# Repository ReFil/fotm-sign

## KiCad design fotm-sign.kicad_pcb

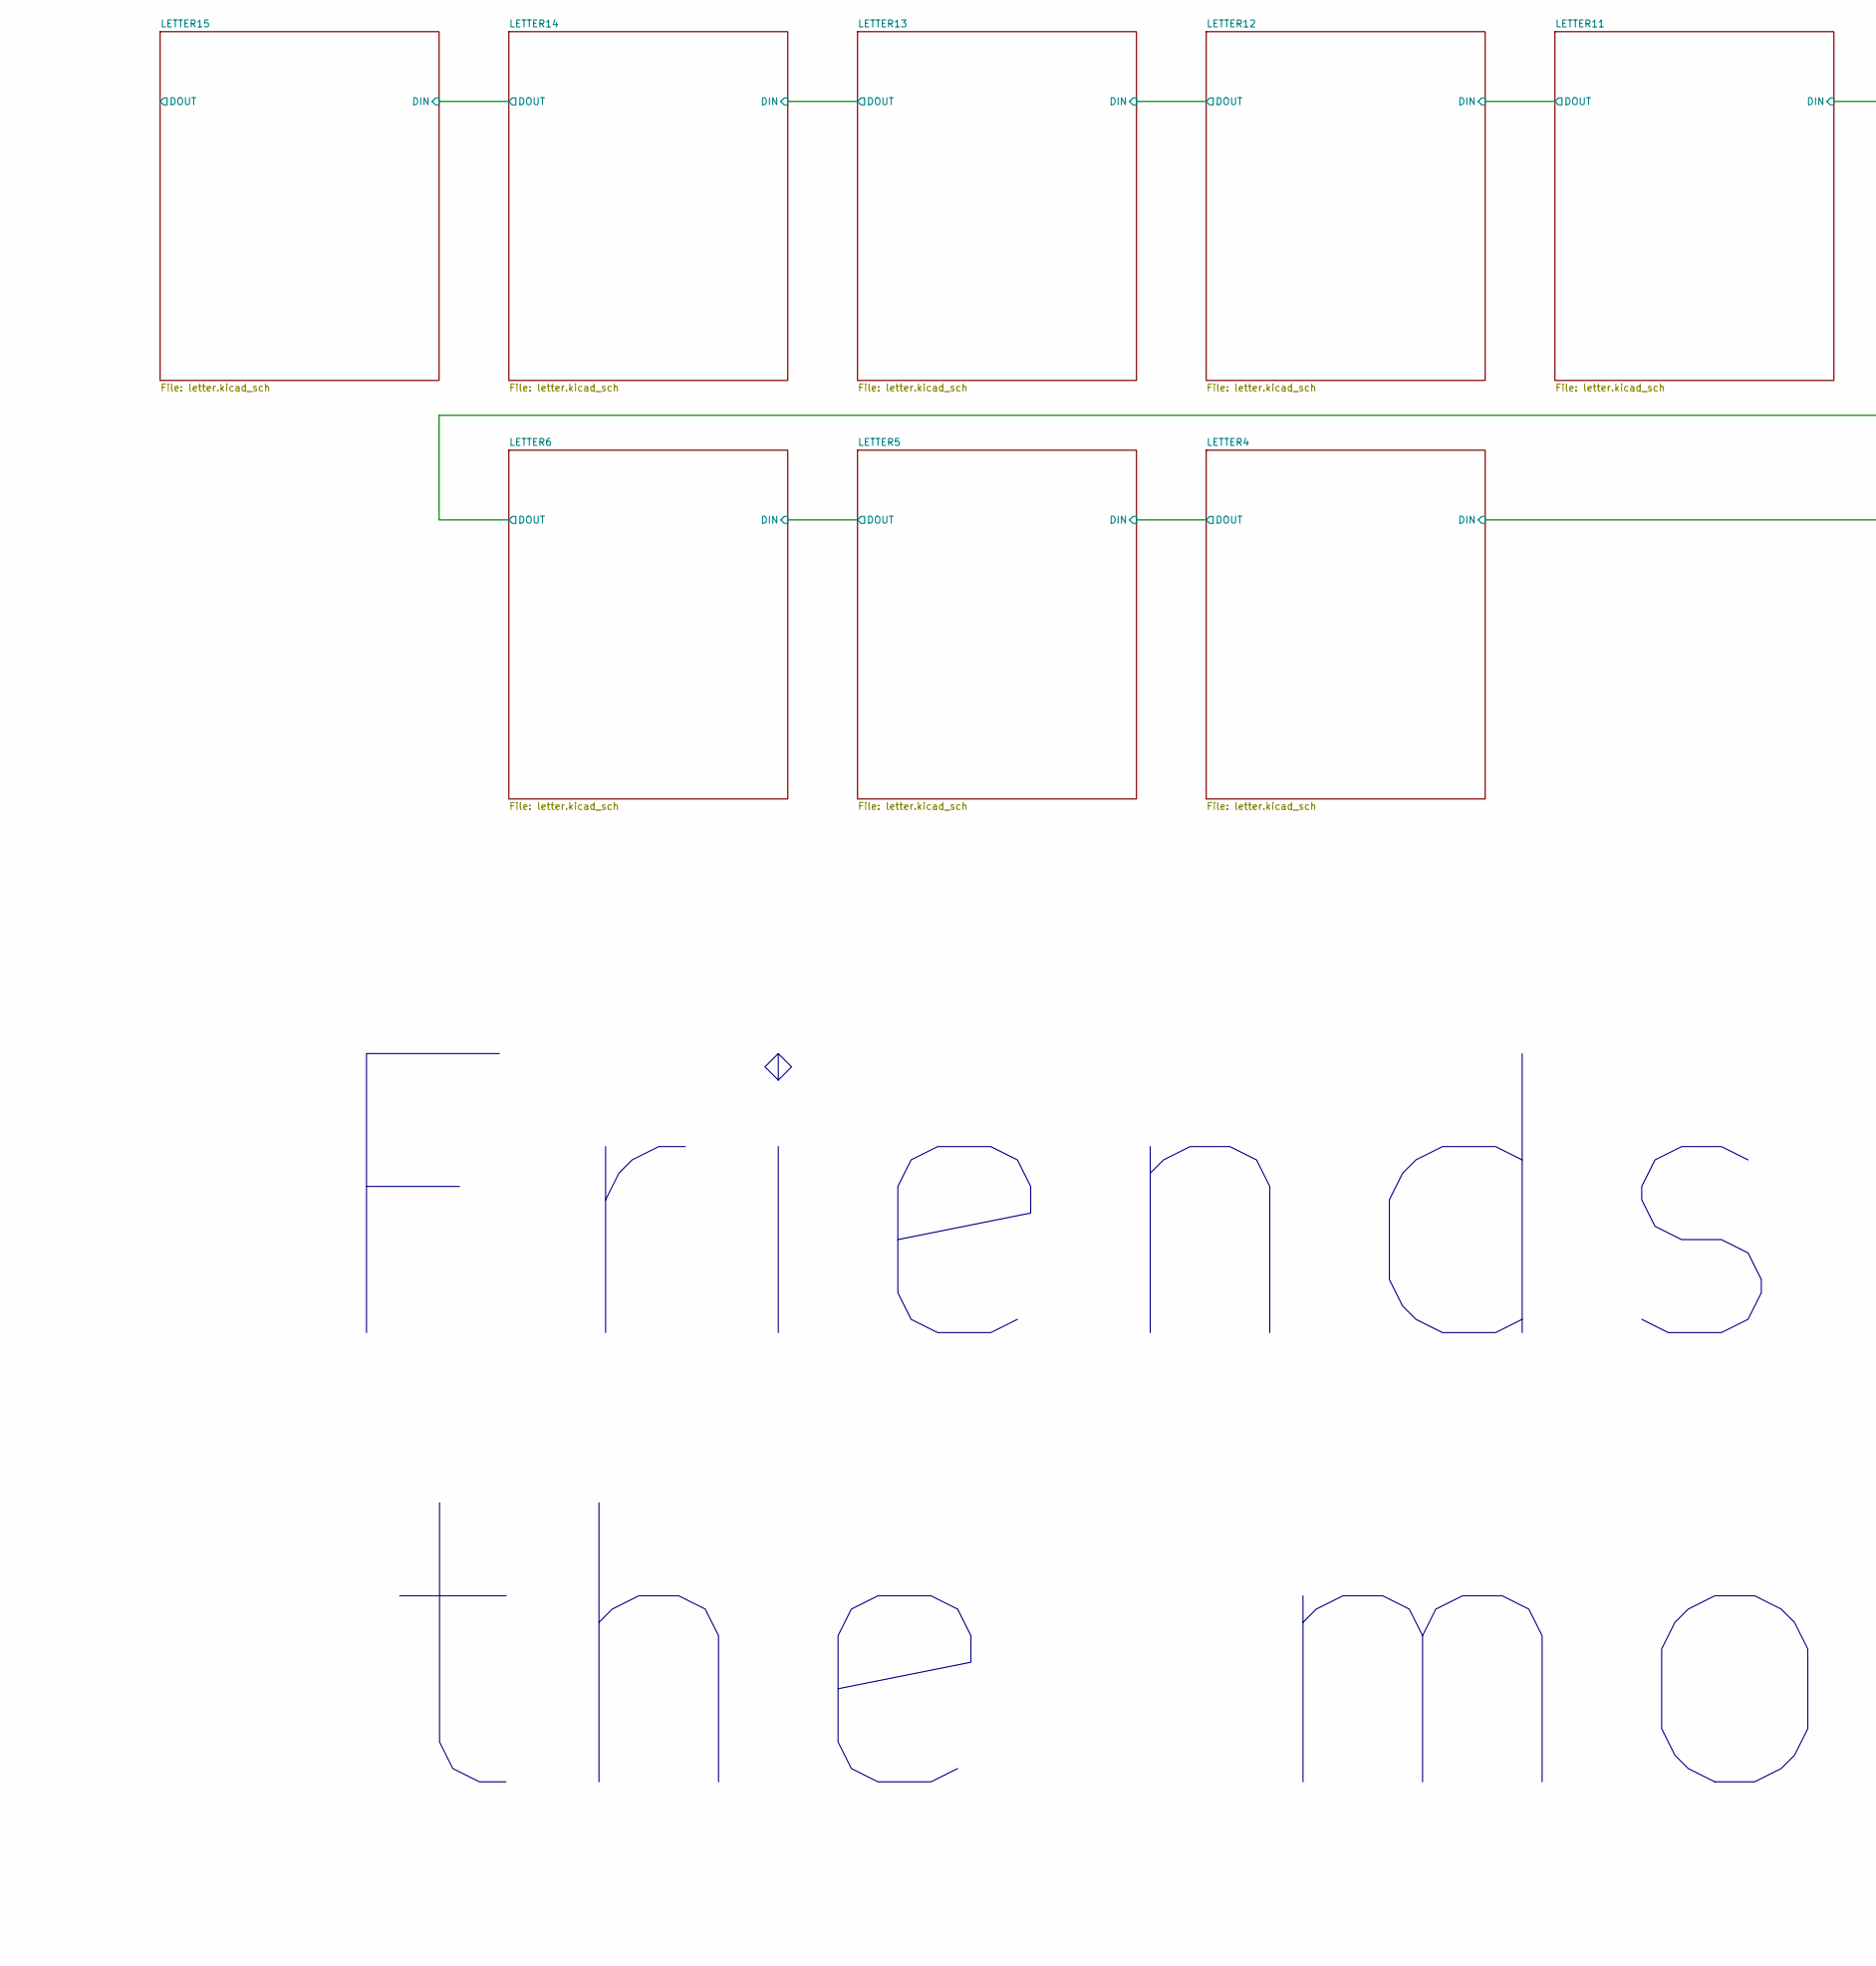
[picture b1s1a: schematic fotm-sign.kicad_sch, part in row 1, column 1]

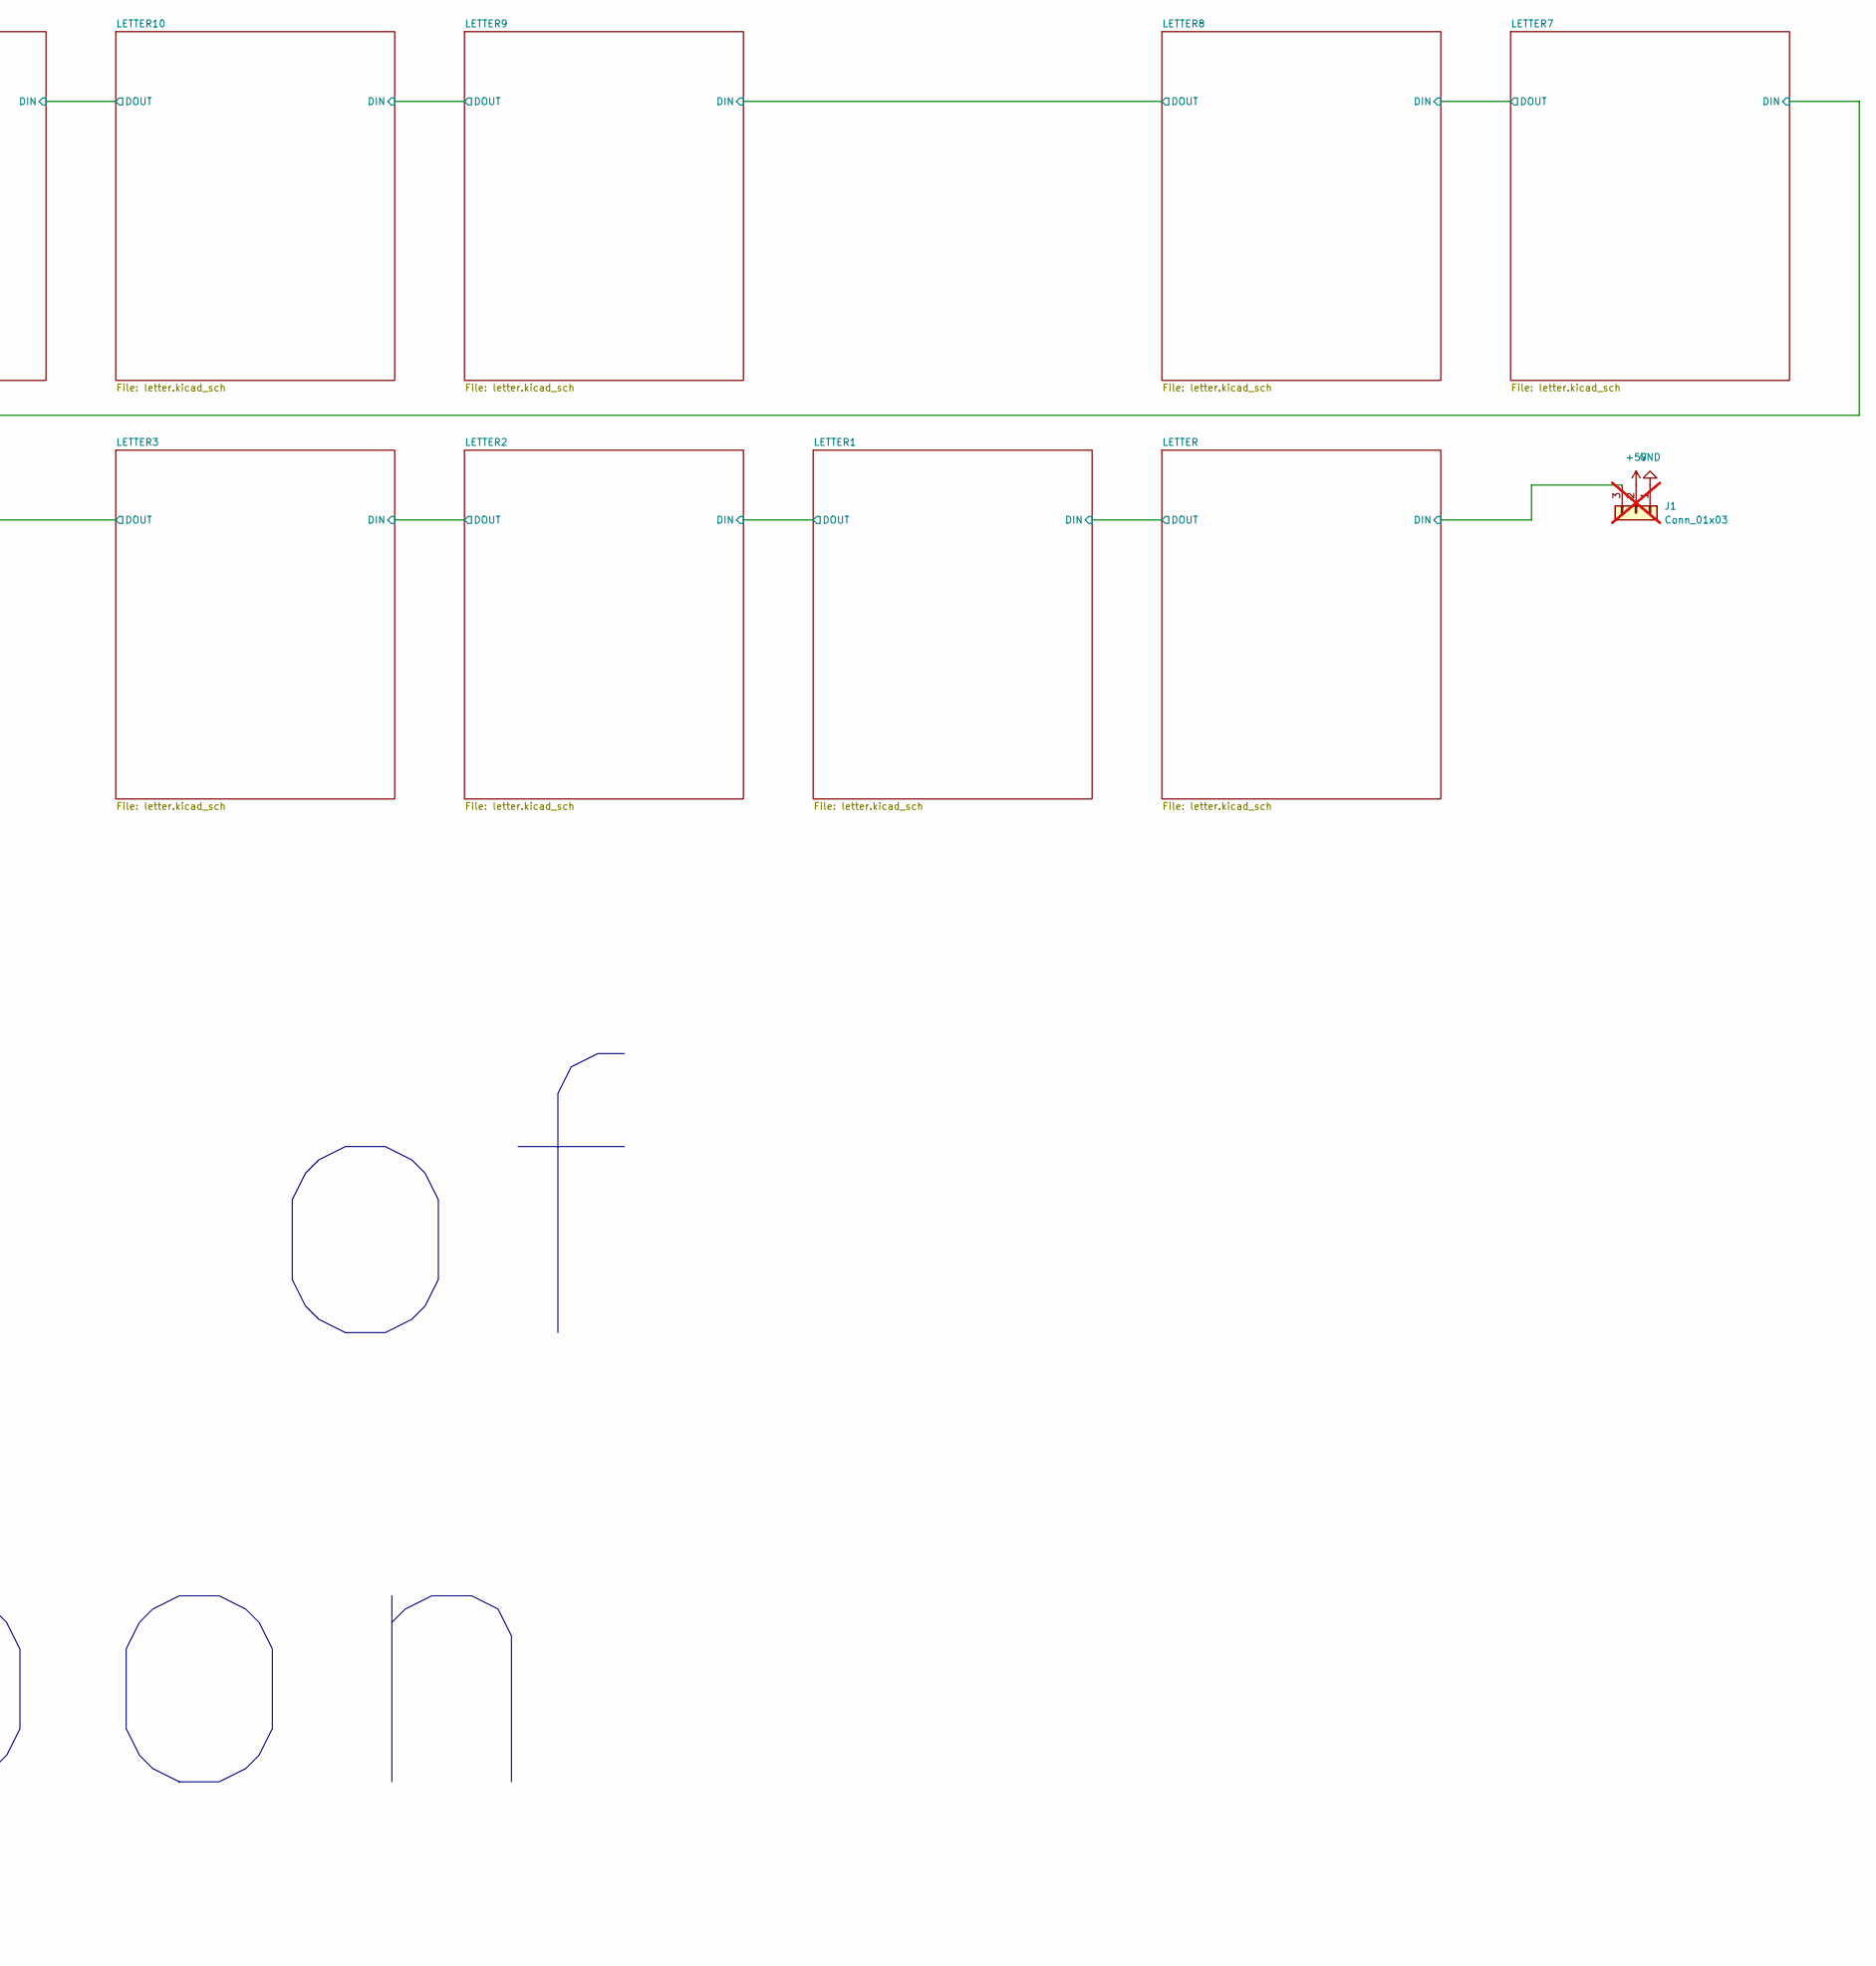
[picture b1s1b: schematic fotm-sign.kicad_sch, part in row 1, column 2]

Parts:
J1: Conn_01x03; PinHeader_1x03_P2.54mm_Vertical; not fitted

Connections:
+5V: J1.2; also elsewhere on the board
/LETTER/DIN: J1.3; also elsewhere on the board
GND: J1.1; also elsewhere on the board

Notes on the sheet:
Friends of the moon

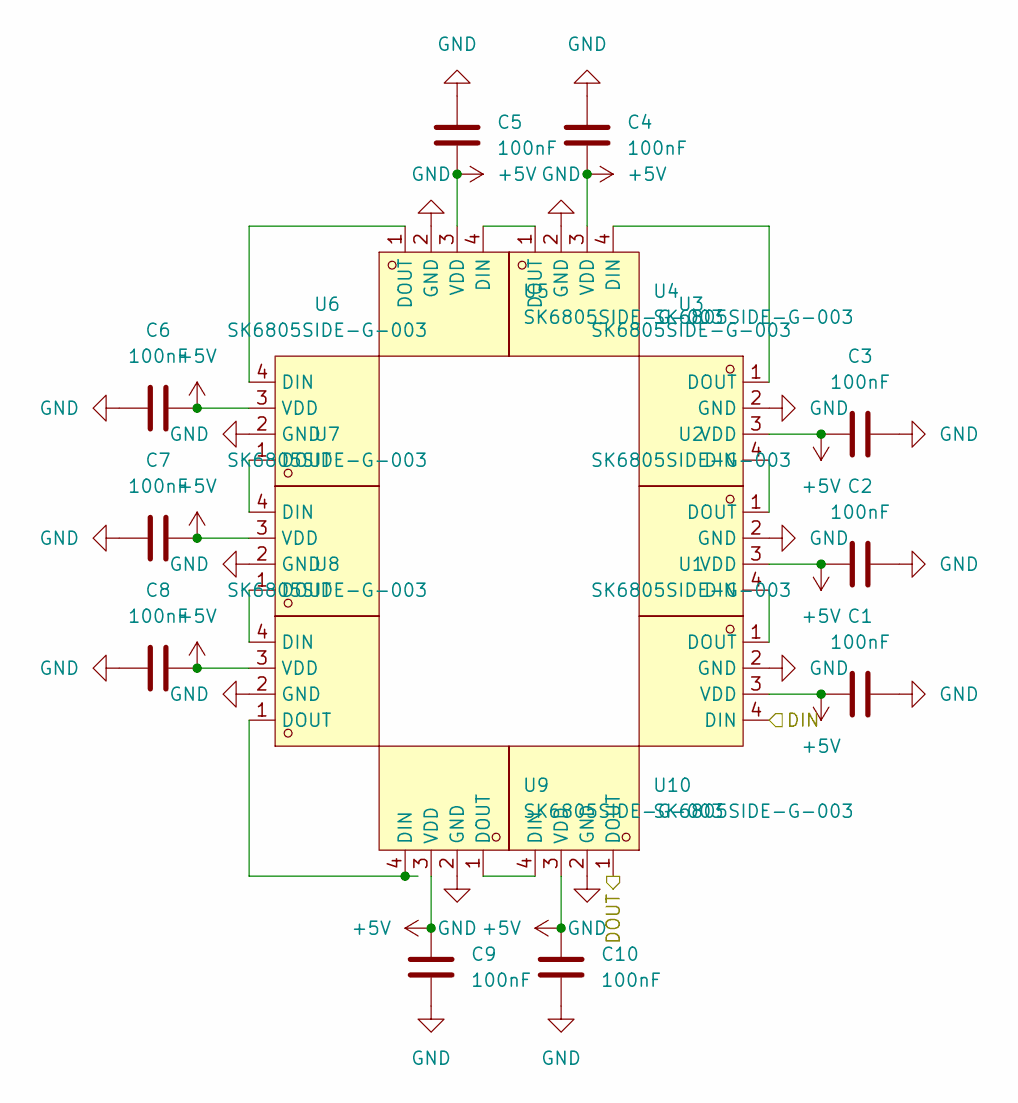
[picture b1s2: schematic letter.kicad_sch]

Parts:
C1, C2, C3, C4, C5, C6, C7, C8, C9, C10: 100nF; C_0402_1005Metric; LCSC Part A
U1, U2, U3, U4, U5, U6, U7, U8, U9, U10: SK6805SIDE-G-003; LED-SMD_4P-L3.5-W1.6_SK6805SIDE-G-001; MPN SK6805SIDE-G-003; LCSC Part C31452139

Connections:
+5V: C1.1, C2.1, C3.1, C4.1, C5.1, C6.1, C7.1, C8.1, C9.1, C10.1, U1.3 (VDD), U2.3 (VDD), U3.3 (VDD), U4.3 (VDD), U5.3 (VDD), U6.3 (VDD), U7.3 (VDD), U8.3 (VDD), U9.3 (VDD), U10.3 (VDD); also elsewhere on the board
/LETTER/DIN: U1.4 (DIN); also elsewhere on the board
/LETTER/DOUT: U10.1 (DOUT); also elsewhere on the board
GND: C1.2, C2.2, C3.2, C4.2, C5.2, C6.2, C7.2, C8.2, C9.2, C10.2, U1.2 (GND), U2.2 (GND), U3.2 (GND), U4.2 (GND), U5.2 (GND), U6.2 (GND), U7.2 (GND), U8.2 (GND), U9.2 (GND), U10.2 (GND); also elsewhere on the board
unnamed: U1.1 (DOUT), U2.4 (DIN)
unnamed: U2.1 (DOUT), U3.4 (DIN)
unnamed: U3.1 (DOUT), U4.4 (DIN)
unnamed: U4.1 (DOUT), U5.4 (DIN)
unnamed: U5.1 (DOUT), U6.4 (DIN)
unnamed: U6.1 (DOUT), U7.4 (DIN)
unnamed: U7.1 (DOUT), U8.4 (DIN)
unnamed: U8.1 (DOUT), U9.4 (DIN)
unnamed: U9.1 (DOUT), U10.4 (DIN)

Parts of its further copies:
C11, C12, C13, C14, C15, C16, C17, C18, C19, C20, C21, C22, C23, C24, C25, C26, C27, C28, C29, C30, C31, C32, C33, C34, C35, C36, C37, C38, C39, C40, C41, C42, C43, C44, C45, C46, C47, C48, C49, C50, C51, C52, C53, C54, C55, C56, C57, C58, C59, C60, C61, C62, C63, C64, C65, C66, C67, C68, C69, C70, C71, C72, C73, C74, C75, C76, C77, C78, C79, C80, C81, C82, C83, C84, C85, C86, C87, C88, C89, C90, C91, C92, C93, C94, C95, C96, C97, C98, C99, C100, C101, C102, C103, C104, C105, C106, C107, C108, C109, C110, C111, C112, C113, C114, C115, C116, C117, C118, C119, C120, C121, C122, C123, C124, C125, C126, C127, C128, C129, C130, C131, C132, C133, C134, C135, C136, C137, C138, C139, C140, C141, C142, C143, C144, C145, C146, C147, C148, C149, C150, C151, C152, C153, C154, C155, C156, C157, C158, C159, C160: 100nF; C_0402_1005Metric; LCSC Part A
U11, U12, U13, U14, U15, U16, U17, U18, U19, U20, U21, U22, U23, U24, U25, U26, U27, U28, U29, U30, U31, U32, U33, U34, U35, U36, U37, U38, U39, U40, U41, U42, U43, U44, U45, U46, U47, U48, U49, U50, U51, U52, U53, U54, U55, U56, U57, U58, U59, U60, U61, U62, U63, U64, U65, U66, U67, U68, U69, U70, U71, U72, U73, U74, U75, U76, U77, U78, U79, U80, U81, U82, U83, U84, U85, U86, U87, U88, U89, U90, U91, U92, U93, U94, U95, U96, U97, U98, U99, U100, U101, U102, U103, U104, U105, U106, U107, U108, U109, U110, U111, U112, U113, U114, U115, U116, U117, U118, U119, U120, U121, U122, U123, U124, U125, U126, U127, U128, U129, U130, U131, U132, U133, U134, U135, U136, U137, U138, U139, U140, U141, U142, U143, U144, U145, U146, U147, U148, U149, U150, U151, U152, U153, U154, U155, U156, U157, U158, U159, U160: SK6805SIDE-G-003; LED-SMD_4P-L3.5-W1.6_SK6805SIDE-G-001; MPN SK6805SIDE-G-003; LCSC Part C31452139

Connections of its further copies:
+5V: C11.1, C12.1, C13.1, C14.1, C15.1, C16.1, C17.1, C18.1, C19.1, C20.1, C21.1, C22.1, C23.1, C24.1, C25.1, C26.1, C27.1, C28.1, C29.1, C30.1, C31.1, C32.1, C33.1, C34.1, C35.1, C36.1, C37.1, C38.1, C39.1, C40.1, C41.1, C42.1, C43.1, C44.1, C45.1, C46.1, C47.1, C48.1, C49.1, C50.1, C51.1, C52.1, C53.1, C54.1, C55.1, C56.1, C57.1, C58.1, C59.1, C60.1, C61.1, C62.1, C63.1, C64.1, C65.1, C66.1, C67.1, C68.1, C69.1, C70.1, C71.1, C72.1, C73.1, C74.1, C75.1, C76.1, C77.1, C78.1, C79.1, C80.1, C81.1, C82.1, C83.1, C84.1, C85.1, C86.1, C87.1, C88.1, C89.1, C90.1, C91.1, C92.1, C93.1, C94.1, C95.1, C96.1, C97.1, C98.1, C99.1, C100.1, C101.1, C102.1, C103.1, C104.1, C105.1, C106.1, C107.1, C108.1, C109.1, C110.1, C111.1, C112.1, C113.1, C114.1, C115.1, C116.1, C117.1, C118.1, C119.1, C120.1, C121.1, C122.1, C123.1, C124.1, C125.1, C126.1, C127.1, C128.1, C129.1, C130.1, C131.1, C132.1, C133.1, C134.1, C135.1, C136.1, C137.1, C138.1, C139.1, C140.1, C141.1, C142.1, C143.1, C144.1, C145.1, C146.1, C147.1, C148.1, C149.1, C150.1, C151.1, C152.1, C153.1, C154.1, C155.1, C156.1, C157.1, C158.1, C159.1, C160.1, U11.3 (VDD), U12.3 (VDD), U13.3 (VDD), U14.3 (VDD), U15.3 (VDD), U16.3 (VDD), U17.3 (VDD), U18.3 (VDD), U19.3 (VDD), U20.3 (VDD), U21.3 (VDD), U22.3 (VDD), U23.3 (VDD), U24.3 (VDD), U25.3 (VDD), U26.3 (VDD), U27.3 (VDD), U28.3 (VDD), U29.3 (VDD), U30.3 (VDD), U31.3 (VDD), U32.3 (VDD), U33.3 (VDD), U34.3 (VDD), U35.3 (VDD), U36.3 (VDD), U37.3 (VDD), U38.3 (VDD), U39.3 (VDD), U40.3 (VDD), U41.3 (VDD), U42.3 (VDD), U43.3 (VDD), U44.3 (VDD), U45.3 (VDD), U46.3 (VDD), U47.3 (VDD), U48.3 (VDD), U49.3 (VDD), U50.3 (VDD), U51.3 (VDD), U52.3 (VDD), U53.3 (VDD), U54.3 (VDD), U55.3 (VDD), U56.3 (VDD), U57.3 (VDD), U58.3 (VDD), U59.3 (VDD), U60.3 (VDD), U61.3 (VDD), U62.3 (VDD), U63.3 (VDD), U64.3 (VDD), U65.3 (VDD), U66.3 (VDD), U67.3 (VDD), U68.3 (VDD), U69.3 (VDD), U70.3 (VDD), U71.3 (VDD), U72.3 (VDD), U73.3 (VDD), U74.3 (VDD), U75.3 (VDD), U76.3 (VDD), U77.3 (VDD), U78.3 (VDD), U79.3 (VDD), U80.3 (VDD), U81.3 (VDD), U82.3 (VDD), U83.3 (VDD), U84.3 (VDD), U85.3 (VDD), U86.3 (VDD), U87.3 (VDD), U88.3 (VDD), U89.3 (VDD), U90.3 (VDD), U91.3 (VDD), U92.3 (VDD), U93.3 (VDD), U94.3 (VDD), U95.3 (VDD), U96.3 (VDD), U97.3 (VDD), U98.3 (VDD), U99.3 (VDD), U100.3 (VDD), U101.3 (VDD), U102.3 (VDD), U103.3 (VDD), U104.3 (VDD), U105.3 (VDD), U106.3 (VDD), U107.3 (VDD), U108.3 (VDD), U109.3 (VDD), U110.3 (VDD), U111.3 (VDD), U112.3 (VDD), U113.3 (VDD), U114.3 (VDD), U115.3 (VDD), U116.3 (VDD), U117.3 (VDD), U118.3 (VDD), U119.3 (VDD), U120.3 (VDD), U121.3 (VDD), U122.3 (VDD), U123.3 (VDD), U124.3 (VDD), U125.3 (VDD), U126.3 (VDD), U127.3 (VDD), U128.3 (VDD), U129.3 (VDD), U130.3 (VDD), U131.3 (VDD), U132.3 (VDD), U133.3 (VDD), U134.3 (VDD), U135.3 (VDD), U136.3 (VDD), U137.3 (VDD), U138.3 (VDD), U139.3 (VDD), U140.3 (VDD), U141.3 (VDD), U142.3 (VDD), U143.3 (VDD), U144.3 (VDD), U145.3 (VDD), U146.3 (VDD), U147.3 (VDD), U148.3 (VDD), U149.3 (VDD), U150.3 (VDD), U151.3 (VDD), U152.3 (VDD), U153.3 (VDD), U154.3 (VDD), U155.3 (VDD), U156.3 (VDD), U157.3 (VDD), U158.3 (VDD), U159.3 (VDD), U160.3 (VDD); also elsewhere on the board
/LETTER1/DOUT: U17.1 (DOUT), U30.4 (DIN)
/LETTER2/DOUT: U27.1 (DOUT), U40.4 (DIN)
/LETTER3/DOUT: U37.1 (DOUT), U50.4 (DIN)
/LETTER4/DOUT: U47.1 (DOUT), U60.4 (DIN)
/LETTER5/DOUT: U57.1 (DOUT), U70.4 (DIN)
/LETTER6/DOUT: U67.1 (DOUT), U80.4 (DIN)
/LETTER7/DOUT: U77.1 (DOUT), U90.4 (DIN)
/LETTER8/DOUT: U87.1 (DOUT), U100.4 (DIN)
/LETTER10/DIN: U97.1 (DOUT), U110.4 (DIN)
/LETTER10/DOUT: U107.1 (DOUT), U120.4 (DIN)
/LETTER11/DOUT: U117.1 (DOUT), U130.4 (DIN)
/LETTER12/DOUT: U127.1 (DOUT), U140.4 (DIN)
/LETTER13/DOUT: U137.1 (DOUT), U150.4 (DIN)
/LETTER14/DOUT: U147.1 (DOUT), U160.4 (DIN)
/LETTER15/DOUT: U157.1 (DOUT)
/LETTER/DOUT: U20.4 (DIN); also elsewhere on the board
GND: C11.2, C12.2, C13.2, C14.2, C15.2, C16.2, C17.2, C18.2, C19.2, C20.2, C21.2, C22.2, C23.2, C24.2, C25.2, C26.2, C27.2, C28.2, C29.2, C30.2, C31.2, C32.2, C33.2, C34.2, C35.2, C36.2, C37.2, C38.2, C39.2, C40.2, C41.2, C42.2, C43.2, C44.2, C45.2, C46.2, C47.2, C48.2, C49.2, C50.2, C51.2, C52.2, C53.2, C54.2, C55.2, C56.2, C57.2, C58.2, C59.2, C60.2, C61.2, C62.2, C63.2, C64.2, C65.2, C66.2, C67.2, C68.2, C69.2, C70.2, C71.2, C72.2, C73.2, C74.2, C75.2, C76.2, C77.2, C78.2, C79.2, C80.2, C81.2, C82.2, C83.2, C84.2, C85.2, C86.2, C87.2, C88.2, C89.2, C90.2, C91.2, C92.2, C93.2, C94.2, C95.2, C96.2, C97.2, C98.2, C99.2, C100.2, C101.2, C102.2, C103.2, C104.2, C105.2, C106.2, C107.2, C108.2, C109.2, C110.2, C111.2, C112.2, C113.2, C114.2, C115.2, C116.2, C117.2, C118.2, C119.2, C120.2, C121.2, C122.2, C123.2, C124.2, C125.2, C126.2, C127.2, C128.2, C129.2, C130.2, C131.2, C132.2, C133.2, C134.2, C135.2, C136.2, C137.2, C138.2, C139.2, C140.2, C141.2, C142.2, C143.2, C144.2, C145.2, C146.2, C147.2, C148.2, C149.2, C150.2, C151.2, C152.2, C153.2, C154.2, C155.2, C156.2, C157.2, C158.2, C159.2, C160.2, U11.2 (GND), U12.2 (GND), U13.2 (GND), U14.2 (GND), U15.2 (GND), U16.2 (GND), U17.2 (GND), U18.2 (GND), U19.2 (GND), U20.2 (GND), U21.2 (GND), U22.2 (GND), U23.2 (GND), U24.2 (GND), U25.2 (GND), U26.2 (GND), U27.2 (GND), U28.2 (GND), U29.2 (GND), U30.2 (GND), U31.2 (GND), U32.2 (GND), U33.2 (GND), U34.2 (GND), U35.2 (GND), U36.2 (GND), U37.2 (GND), U38.2 (GND), U39.2 (GND), U40.2 (GND), U41.2 (GND), U42.2 (GND), U43.2 (GND), U44.2 (GND), U45.2 (GND), U46.2 (GND), U47.2 (GND), U48.2 (GND), U49.2 (GND), U50.2 (GND), U51.2 (GND), U52.2 (GND), U53.2 (GND), U54.2 (GND), U55.2 (GND), U56.2 (GND), U57.2 (GND), U58.2 (GND), U59.2 (GND), U60.2 (GND), U61.2 (GND), U62.2 (GND), U63.2 (GND), U64.2 (GND), U65.2 (GND), U66.2 (GND), U67.2 (GND), U68.2 (GND), U69.2 (GND), U70.2 (GND), U71.2 (GND), U72.2 (GND), U73.2 (GND), U74.2 (GND), U75.2 (GND), U76.2 (GND), U77.2 (GND), U78.2 (GND), U79.2 (GND), U80.2 (GND), U81.2 (GND), U82.2 (GND), U83.2 (GND), U84.2 (GND), U85.2 (GND), U86.2 (GND), U87.2 (GND), U88.2 (GND), U89.2 (GND), U90.2 (GND), U91.2 (GND), U92.2 (GND), U93.2 (GND), U94.2 (GND), U95.2 (GND), U96.2 (GND), U97.2 (GND), U98.2 (GND), U99.2 (GND), U100.2 (GND), U101.2 (GND), U102.2 (GND), U103.2 (GND), U104.2 (GND), U105.2 (GND), U106.2 (GND), U107.2 (GND), U108.2 (GND), U109.2 (GND), U110.2 (GND), U111.2 (GND), U112.2 (GND), U113.2 (GND), U114.2 (GND), U115.2 (GND), U116.2 (GND), U117.2 (GND), U118.2 (GND), U119.2 (GND), U120.2 (GND), U121.2 (GND), U122.2 (GND), U123.2 (GND), U124.2 (GND), U125.2 (GND), U126.2 (GND), U127.2 (GND), U128.2 (GND), U129.2 (GND), U130.2 (GND), U131.2 (GND), U132.2 (GND), U133.2 (GND), U134.2 (GND), U135.2 (GND), U136.2 (GND), U137.2 (GND), U138.2 (GND), U139.2 (GND), U140.2 (GND), U141.2 (GND), U142.2 (GND), U143.2 (GND), U144.2 (GND), U145.2 (GND), U146.2 (GND), U147.2 (GND), U148.2 (GND), U149.2 (GND), U150.2 (GND), U151.2 (GND), U152.2 (GND), U153.2 (GND), U154.2 (GND), U155.2 (GND), U156.2 (GND), U157.2 (GND), U158.2 (GND), U159.2 (GND), U160.2 (GND); also elsewhere on the board
unnamed: U11.4 (DIN), U14.1 (DOUT)
unnamed: U11.1 (DOUT), U12.4 (DIN)
unnamed: U12.1 (DOUT), U13.4 (DIN)
unnamed: U13.1 (DOUT), U15.4 (DIN)
unnamed: U14.4 (DIN), U16.1 (DOUT)
unnamed: U15.1 (DOUT), U17.4 (DIN)
unnamed: U16.4 (DIN), U18.1 (DOUT)
unnamed: U18.4 (DIN), U19.1 (DOUT)
unnamed: U19.4 (DIN), U20.1 (DOUT)
unnamed: U21.4 (DIN), U24.1 (DOUT)
unnamed: U21.1 (DOUT), U22.4 (DIN)
unnamed: U22.1 (DOUT), U23.4 (DIN)
unnamed: U23.1 (DOUT), U25.4 (DIN)
unnamed: U24.4 (DIN), U26.1 (DOUT)
unnamed: U25.1 (DOUT), U27.4 (DIN)
unnamed: U26.4 (DIN), U28.1 (DOUT)
unnamed: U28.4 (DIN), U29.1 (DOUT)
unnamed: U29.4 (DIN), U30.1 (DOUT)
unnamed: U31.4 (DIN), U34.1 (DOUT)
unnamed: U31.1 (DOUT), U32.4 (DIN)
unnamed: U32.1 (DOUT), U33.4 (DIN)
unnamed: U33.1 (DOUT), U35.4 (DIN)
unnamed: U34.4 (DIN), U36.1 (DOUT)
unnamed: U35.1 (DOUT), U37.4 (DIN)
unnamed: U36.4 (DIN), U38.1 (DOUT)
unnamed: U38.4 (DIN), U39.1 (DOUT)
unnamed: U39.4 (DIN), U40.1 (DOUT)
unnamed: U41.4 (DIN), U44.1 (DOUT)
unnamed: U41.1 (DOUT), U42.4 (DIN)
unnamed: U42.1 (DOUT), U43.4 (DIN)
unnamed: U43.1 (DOUT), U45.4 (DIN)
unnamed: U44.4 (DIN), U46.1 (DOUT)
unnamed: U45.1 (DOUT), U47.4 (DIN)
unnamed: U46.4 (DIN), U48.1 (DOUT)
unnamed: U48.4 (DIN), U49.1 (DOUT)
unnamed: U49.4 (DIN), U50.1 (DOUT)
unnamed: U51.4 (DIN), U54.1 (DOUT)
unnamed: U51.1 (DOUT), U52.4 (DIN)
unnamed: U52.1 (DOUT), U53.4 (DIN)
unnamed: U53.1 (DOUT), U55.4 (DIN)
unnamed: U54.4 (DIN), U56.1 (DOUT)
unnamed: U55.1 (DOUT), U57.4 (DIN)
unnamed: U56.4 (DIN), U58.1 (DOUT)
unnamed: U58.4 (DIN), U59.1 (DOUT)
unnamed: U59.4 (DIN), U60.1 (DOUT)
unnamed: U61.4 (DIN), U64.1 (DOUT)
unnamed: U61.1 (DOUT), U62.4 (DIN)
unnamed: U62.1 (DOUT), U63.4 (DIN)
unnamed: U63.1 (DOUT), U65.4 (DIN)
unnamed: U64.4 (DIN), U66.1 (DOUT)
unnamed: U65.1 (DOUT), U67.4 (DIN)
unnamed: U66.4 (DIN), U68.1 (DOUT)
unnamed: U68.4 (DIN), U69.1 (DOUT)
unnamed: U69.4 (DIN), U70.1 (DOUT)
unnamed: U71.4 (DIN), U74.1 (DOUT)
unnamed: U71.1 (DOUT), U72.4 (DIN)
unnamed: U72.1 (DOUT), U73.4 (DIN)
unnamed: U73.1 (DOUT), U75.4 (DIN)
unnamed: U74.4 (DIN), U76.1 (DOUT)
unnamed: U75.1 (DOUT), U77.4 (DIN)
unnamed: U76.4 (DIN), U78.1 (DOUT)
unnamed: U78.4 (DIN), U79.1 (DOUT)
unnamed: U79.4 (DIN), U80.1 (DOUT)
unnamed: U81.4 (DIN), U84.1 (DOUT)
unnamed: U81.1 (DOUT), U82.4 (DIN)
unnamed: U82.1 (DOUT), U83.4 (DIN)
unnamed: U83.1 (DOUT), U85.4 (DIN)
unnamed: U84.4 (DIN), U86.1 (DOUT)
unnamed: U85.1 (DOUT), U87.4 (DIN)
unnamed: U86.4 (DIN), U88.1 (DOUT)
unnamed: U88.4 (DIN), U89.1 (DOUT)
unnamed: U89.4 (DIN), U90.1 (DOUT)
unnamed: U91.4 (DIN), U94.1 (DOUT)
unnamed: U91.1 (DOUT), U92.4 (DIN)
unnamed: U92.1 (DOUT), U93.4 (DIN)
unnamed: U93.1 (DOUT), U95.4 (DIN)
unnamed: U94.4 (DIN), U96.1 (DOUT)
unnamed: U95.1 (DOUT), U97.4 (DIN)
unnamed: U96.4 (DIN), U98.1 (DOUT)
unnamed: U98.4 (DIN), U99.1 (DOUT)
unnamed: U99.4 (DIN), U100.1 (DOUT)
unnamed: U101.4 (DIN), U104.1 (DOUT)
unnamed: U101.1 (DOUT), U102.4 (DIN)
unnamed: U102.1 (DOUT), U103.4 (DIN)
unnamed: U103.1 (DOUT), U105.4 (DIN)
unnamed: U104.4 (DIN), U106.1 (DOUT)
unnamed: U105.1 (DOUT), U107.4 (DIN)
unnamed: U106.4 (DIN), U108.1 (DOUT)
unnamed: U108.4 (DIN), U109.1 (DOUT)
unnamed: U109.4 (DIN), U110.1 (DOUT)
unnamed: U111.4 (DIN), U114.1 (DOUT)
unnamed: U111.1 (DOUT), U112.4 (DIN)
unnamed: U112.1 (DOUT), U113.4 (DIN)
unnamed: U113.1 (DOUT), U115.4 (DIN)
unnamed: U114.4 (DIN), U116.1 (DOUT)
unnamed: U115.1 (DOUT), U117.4 (DIN)
unnamed: U116.4 (DIN), U118.1 (DOUT)
unnamed: U118.4 (DIN), U119.1 (DOUT)
unnamed: U119.4 (DIN), U120.1 (DOUT)
unnamed: U121.4 (DIN), U124.1 (DOUT)
unnamed: U121.1 (DOUT), U122.4 (DIN)
unnamed: U122.1 (DOUT), U123.4 (DIN)
unnamed: U123.1 (DOUT), U125.4 (DIN)
unnamed: U124.4 (DIN), U126.1 (DOUT)
unnamed: U125.1 (DOUT), U127.4 (DIN)
unnamed: U126.4 (DIN), U128.1 (DOUT)
unnamed: U128.4 (DIN), U129.1 (DOUT)
unnamed: U129.4 (DIN), U130.1 (DOUT)
unnamed: U131.4 (DIN), U134.1 (DOUT)
unnamed: U131.1 (DOUT), U132.4 (DIN)
unnamed: U132.1 (DOUT), U133.4 (DIN)
unnamed: U133.1 (DOUT), U135.4 (DIN)
unnamed: U134.4 (DIN), U136.1 (DOUT)
unnamed: U135.1 (DOUT), U137.4 (DIN)
unnamed: U136.4 (DIN), U138.1 (DOUT)
unnamed: U138.4 (DIN), U139.1 (DOUT)
unnamed: U139.4 (DIN), U140.1 (DOUT)
unnamed: U141.4 (DIN), U144.1 (DOUT)
unnamed: U141.1 (DOUT), U142.4 (DIN)
unnamed: U142.1 (DOUT), U143.4 (DIN)
unnamed: U143.1 (DOUT), U145.4 (DIN)
unnamed: U144.4 (DIN), U146.1 (DOUT)
unnamed: U145.1 (DOUT), U147.4 (DIN)
unnamed: U146.4 (DIN), U148.1 (DOUT)
unnamed: U148.4 (DIN), U149.1 (DOUT)
unnamed: U149.4 (DIN), U150.1 (DOUT)
unnamed: U151.4 (DIN), U154.1 (DOUT)
unnamed: U151.1 (DOUT), U152.4 (DIN)
unnamed: U152.1 (DOUT), U153.4 (DIN)
unnamed: U153.1 (DOUT), U155.4 (DIN)
unnamed: U154.4 (DIN), U156.1 (DOUT)
unnamed: U155.1 (DOUT), U157.4 (DIN)
unnamed: U156.4 (DIN), U158.1 (DOUT)
unnamed: U158.4 (DIN), U159.1 (DOUT)
unnamed: U159.4 (DIN), U160.1 (DOUT)

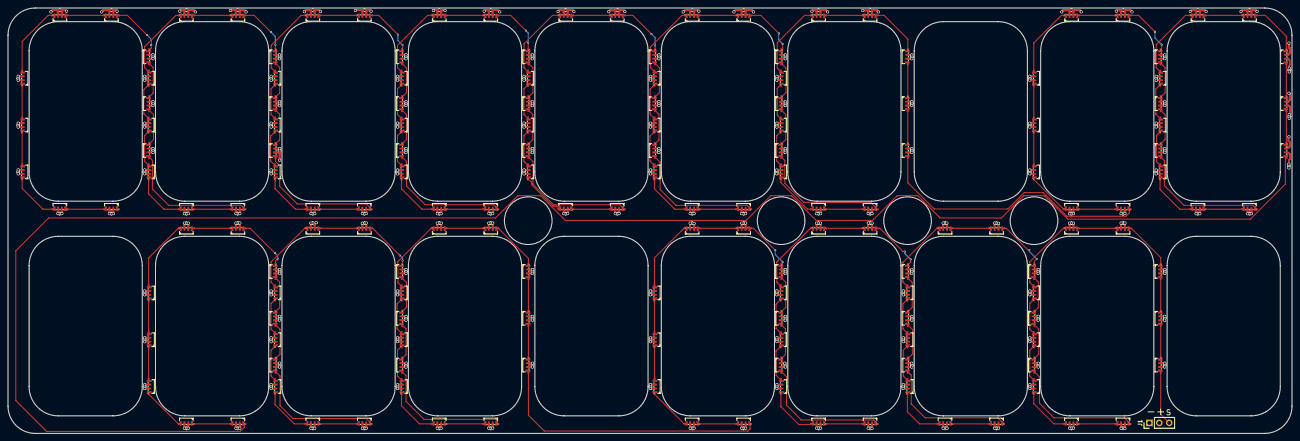
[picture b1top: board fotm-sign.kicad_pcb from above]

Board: 4 copper layers, 329.0 x 109.0 mm, 321 parts (0 on the bottom side), 162 nets.

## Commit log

2026-06-27 gbra
2026-06-27 tweaks
2026-06-27 smdattr
